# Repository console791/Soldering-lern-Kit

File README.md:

# Soldering-learn-Kit
A Small Soldering kit to tech how to solder and will then be a Calculator

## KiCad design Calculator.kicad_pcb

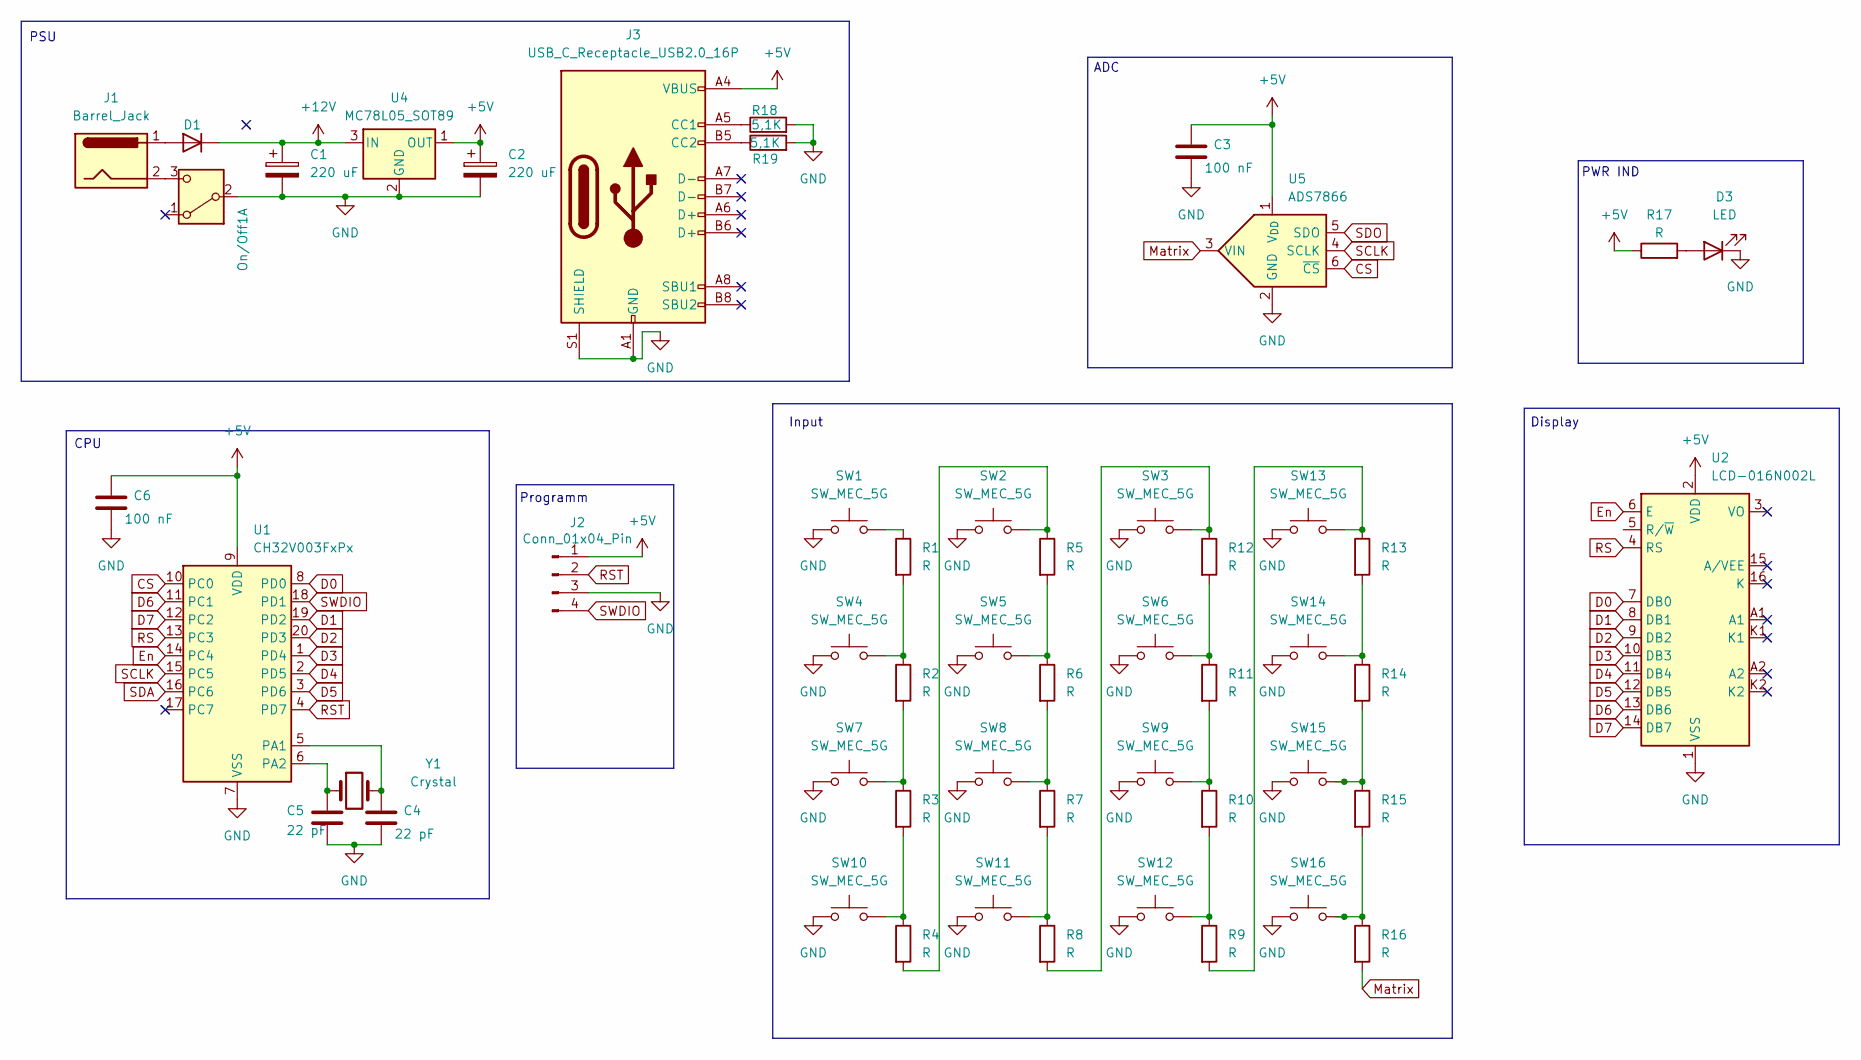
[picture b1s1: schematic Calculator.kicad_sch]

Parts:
C1, C2: 220 uF; CP_Radial_D4.0mm_P1.50mm
C3, C6: 100 nF; C_1206_3216Metric_Pad1.33x1.80mm_HandSolder
C4, C5: 22 pF; C_1206_3216Metric_Pad1.33x1.80mm_HandSolder
D1: 1N4148WT; D_SOD-523
D3: LED; LED_2010_5025Metric
J1: Barrel_Jack; BarrelJack_SwitchcraftConxall_RAPC10U_Horizontal
J2: Conn_01x04_Pin; NS-Tech_Grove_1x04_P2mm_Vertical
J3: USB_C_Receptacle_USB2.0_16P; USB_C_Receptacle_G-Switch_GT-USB-7010ASV
On/Off1: SW_DPDT_x2; SW_CK_JS202011AQN_DPDT_Angled
R1, R2, R3, R4, R5, R6, R7, R8, R9, R10, R11, R12, R13, R14, R15, R16, R17: R; R_2010_5025Metric_Pad1.40x2.65mm_HandSolder
R18, R19: 5,1K; R_2010_5025Metric_Pad1.40x2.65mm_HandSolder
SW1, SW2, SW3, SW4, SW5, SW6, SW7, SW8, SW9, SW10, SW11, SW12, SW13, SW14, SW15, SW16: SW_MEC_5G; SW_MEC_5GSH9
U1: CH32V003FxPx; TSSOP-20_4.4x6.5mm_P0.65mm
U2: LCD-016N002L
U4: MC78L05_SOT89; SOT-89-3_Handsoldering
U5: ADS7866; SOT-23-6_Handsoldering
Y1: Crystal; Crystal_HC18-U_Vertical

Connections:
+5V: C2.1, C3.1, C6.1, J2.1, J3.A4 (VBUS), J3.A9 (VBUS), J3.B4 (VBUS), J3.B9 (VBUS), R17.1, U1.9 (VDD), U2.2 (VDD), U4.1 (OUT), U5.1 (V_{DD})
+12V: C1.1, D1.1 (K), U4.3 (IN)
CS: U1.10 (PC0), U5.6 (~CS)
D0: U1.8 (PD0), U2.7 (DB0)
D1: U1.19 (PD2), U2.8 (DB1)
D2: U1.20 (PD3), U2.9 (DB2)
D3: U1.1 (PD4), U2.10 (DB3)
D4: U1.2 (PD5), U2.11 (DB4)
D5: U1.3 (PD6), U2.12 (DB5)
D6: U1.11 (PC1), U2.13 (DB6)
D7: U1.12 (PC2), U2.14 (DB7)
En: U1.14 (PC4), U2.6 (E)
GND: C1.2, C2.2, C3.2, C4.2, C5.2, C6.2, D3.1 (K), J2.3, J3.A1 (GND), J3.A12 (GND), J3.B1 (GND), J3.B12 (GND), J3.S1 (SHIELD), On/Off1.2 (B), R18.2, R19.2, SW1.1 (A), SW1.2 (A), SW2.1 (A), SW2.2 (A), SW3.1 (A), SW3.2 (A), SW4.1 (A), SW4.2 (A), SW5.1 (A), SW5.2 (A), SW6.1 (A), SW6.2 (A), SW7.1 (A), SW7.2 (A), SW8.1 (A), SW8.2 (A), SW9.1 (A), SW9.2 (A), SW10.1 (A), SW10.2 (A), SW11.1 (A), SW11.2 (A), SW12.1 (A), SW12.2 (A), SW13.1 (A), SW13.2 (A), SW14.1 (A), SW14.2 (A), SW15.1 (A), SW15.2 (A), SW16.1 (A), SW16.2 (A), U1.7 (VSS), U2.1 (VSS), U4.2 (GND), U5.2 (GND)
Matrix: R16.2, U5.3 (VIN)
unnamed: D1.2 (A), J1.1
unnamed: D3.2 (A), R17.2
unnamed: J3.A5 (CC1), R18.1
unnamed: J3.B5 (CC2), R19.1
unnamed: J1.2, On/Off1.3 (C)
unnamed: R1.1, SW1.3 (B), SW1.4 (B)
unnamed: R1.2, R2.1, SW4.3 (B), SW4.4 (B)
unnamed: R2.2, R3.1, SW7.3 (B), SW7.4 (B)
unnamed: R3.2, R4.1, SW10.3 (B), SW10.4 (B)
unnamed: R4.2, R5.1, SW2.3 (B), SW2.4 (B)
unnamed: R5.2, R6.1, SW5.3 (B), SW5.4 (B)
unnamed: R6.2, R7.1, SW8.3 (B), SW8.4 (B)
unnamed: R7.2, R8.1, SW11.3 (B), SW11.4 (B)
unnamed: R10.1, R11.2, SW9.3 (B), SW9.4 (B)
unnamed: R9.1, R10.2, SW12.3 (B), SW12.4 (B)
unnamed: R11.1, R12.2, SW6.3 (B), SW6.4 (B)
unnamed: R8.2, R12.1, SW3.3 (B), SW3.4 (B)
unnamed: R9.2, R13.1, SW13.3 (B), SW13.4 (B)
unnamed: R13.2, R14.1, SW14.3 (B), SW14.4 (B)
unnamed: R14.2, R15.1, SW15.3 (B), SW15.4 (B)
unnamed: R15.2, R16.1, SW16.3 (B), SW16.4 (B)
unnamed: C4.1, U1.5 (PA1), Y1.2
unnamed: C5.1, U1.6 (PA2), Y1.1
RS: U1.13 (PC3), U2.4 (RS)
RST: J2.2, U1.4 (PD7)
SCLK: U1.15 (PC5), U5.4 (SCLK)
SDA: U1.16 (PC6)
SDO: U5.5 (SDO)
SWDIO: J2.4, U1.18 (PD1)

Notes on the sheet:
Input
ADC
CPU
Programm
PSU
PWR IND
Display

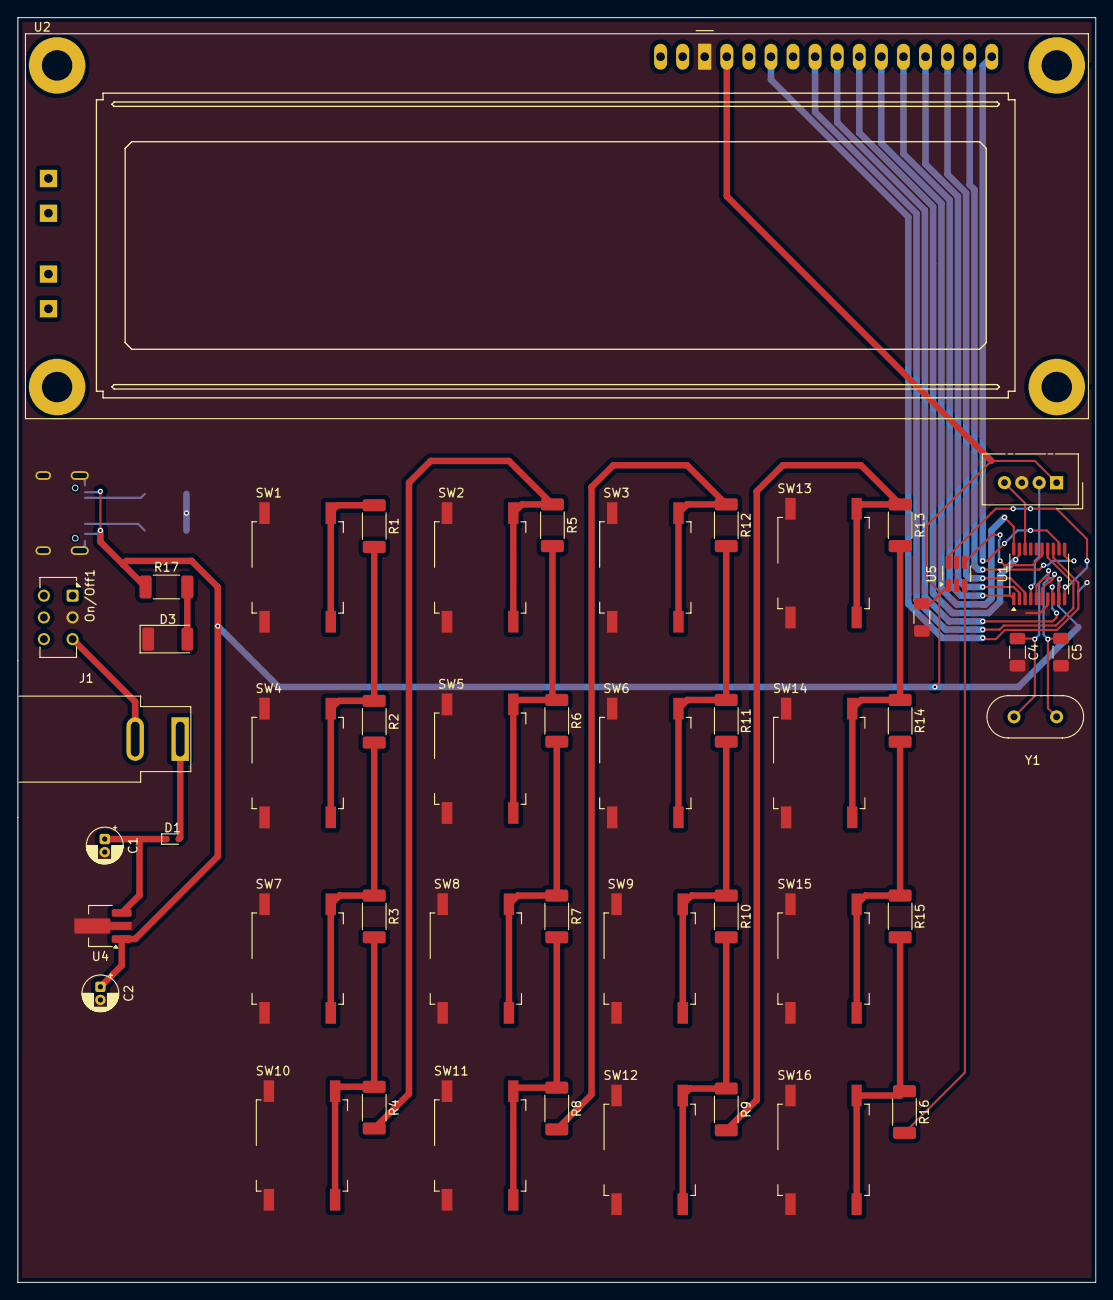
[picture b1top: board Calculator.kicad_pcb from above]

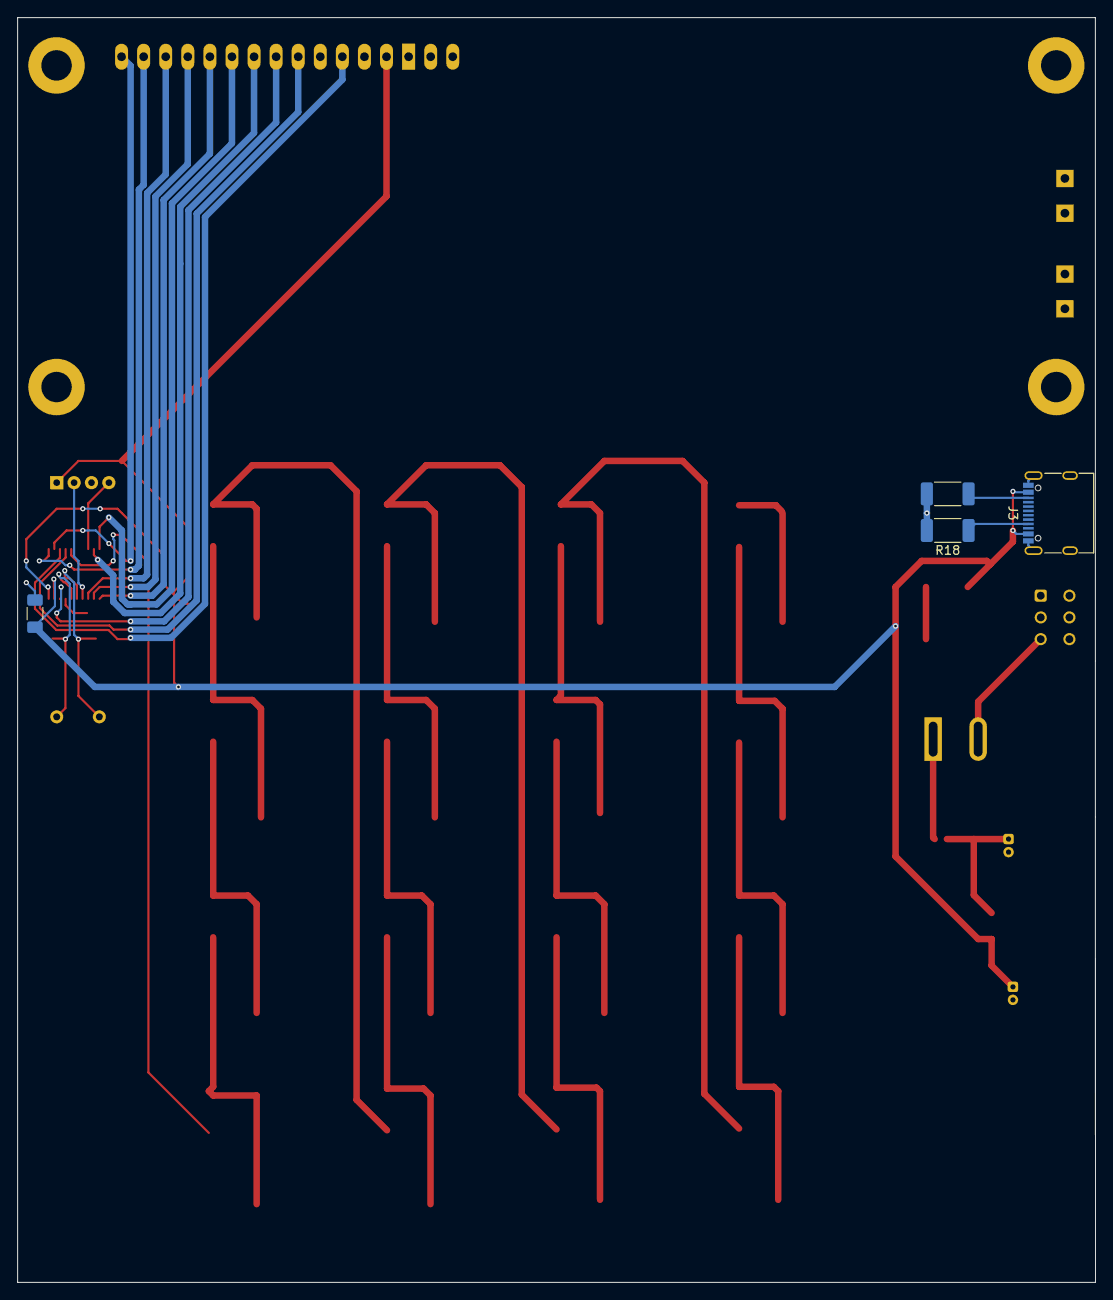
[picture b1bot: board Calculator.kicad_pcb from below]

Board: 2 copper layers, 124.0 x 145.5 mm, 52 parts (4 on the bottom side), 41 nets.
